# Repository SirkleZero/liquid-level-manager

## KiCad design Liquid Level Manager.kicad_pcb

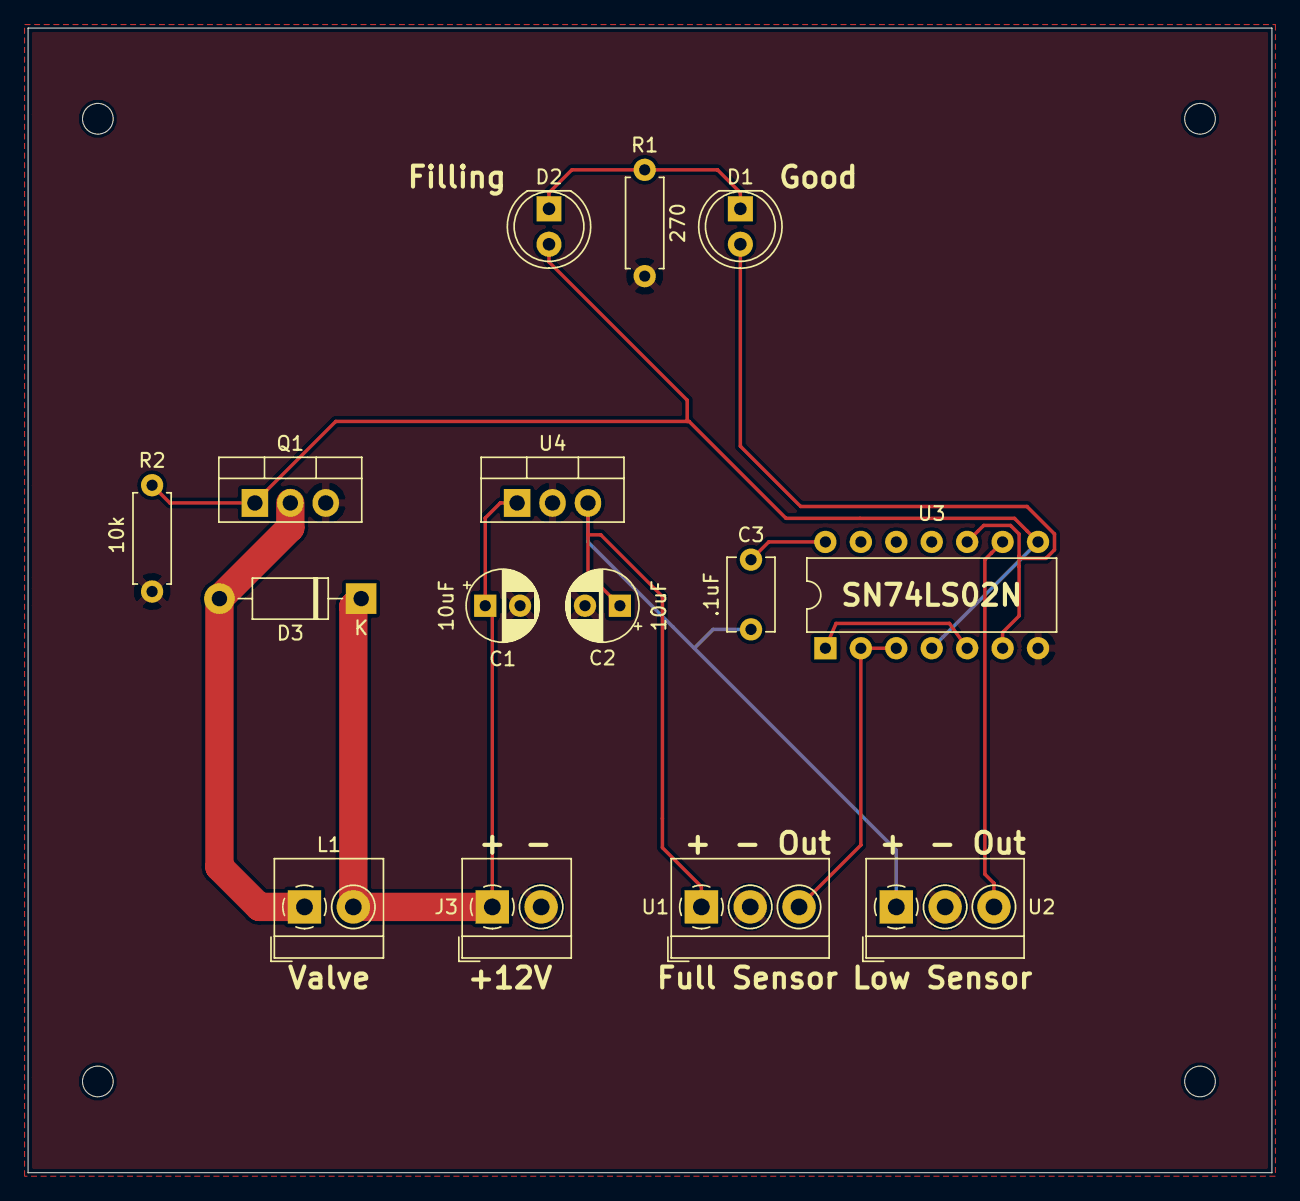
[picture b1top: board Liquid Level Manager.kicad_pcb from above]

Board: 2 copper layers, 89.2 x 82.0 mm, 15 parts (0 on the bottom side), 11 nets.

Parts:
C1, C2: 10uF; CP_Radial_D5.0mm_P2.50mm
C3: .1uF; C_Disc_D5.1mm_W3.2mm_P5.00mm
D1: Good; LED_D5.0mm
D2: Filling; LED_D5.0mm
D3: 1N4001; D_DO-41_SOD81_P10.16mm_Horizontal
J3: +12V; TerminalBlock_4Ucon_1x02_P3.50mm_Horizontal
L1: Valve; TerminalBlock_4Ucon_1x02_P3.50mm_Horizontal
Q1: IRLB8721PBF; TO-220-3_Vertical
R1: 270; R_Axial_DIN0207_L6.3mm_D2.5mm_P7.62mm_Horizontal
R2: 10k; R_Axial_DIN0207_L6.3mm_D2.5mm_P7.62mm_Horizontal
U1: High Sensor; TerminalBlock_4Ucon_1x03_P3.50mm_Horizontal
U2: Low Sensor; TerminalBlock_4Ucon_1x03_P3.50mm_Horizontal
U3: 74LS02; DIP-14_W7.62mm
U4: LM7805C; TO-220-3_Vertical

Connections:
+5V: C2.1, C3.2, U1.1, U2.1, U4.3
+12V: C1.1, D3.1, J3.1, L1.2, U4.1
GND: C1.2, C2.2, J3.2, Q1.3, R1.1, R2.1, U1.2, U2.2, U3.7, U4.2
unnamed: C3.1, U3.14
unnamed: D1.1, D2.1, R1.2
unnamed: D1.2, U3.6, U3.10
unnamed: D3.2, L1.1, Q1.2
unnamed: U1.3, U3.2, U3.3
unnamed: U2.3, U3.9
unnamed: U3.1, U3.5
SENSOR_OUT: D2.2, Q1.1, R2.2, U3.4, U3.8

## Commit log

2018-12-07 initial load
2018-12-11 added a png of the schematic
2018-12-13 poking at the schema a bit
2018-12-18 small schema change and pcb tweaks
2018-12-18 cleaned up the schematic, working on pcb
2018-12-18 moving labels around the schematic
2018-12-18 updated design rules
2018-12-18 added custom trace width for high-current power
2018-12-18 working on trace layout
2018-12-19 schematic and pcb updates
2018-12-19 added a label for the NOR gate chip
2018-12-19 modified revision label
2018-12-19 changed a sensor label
